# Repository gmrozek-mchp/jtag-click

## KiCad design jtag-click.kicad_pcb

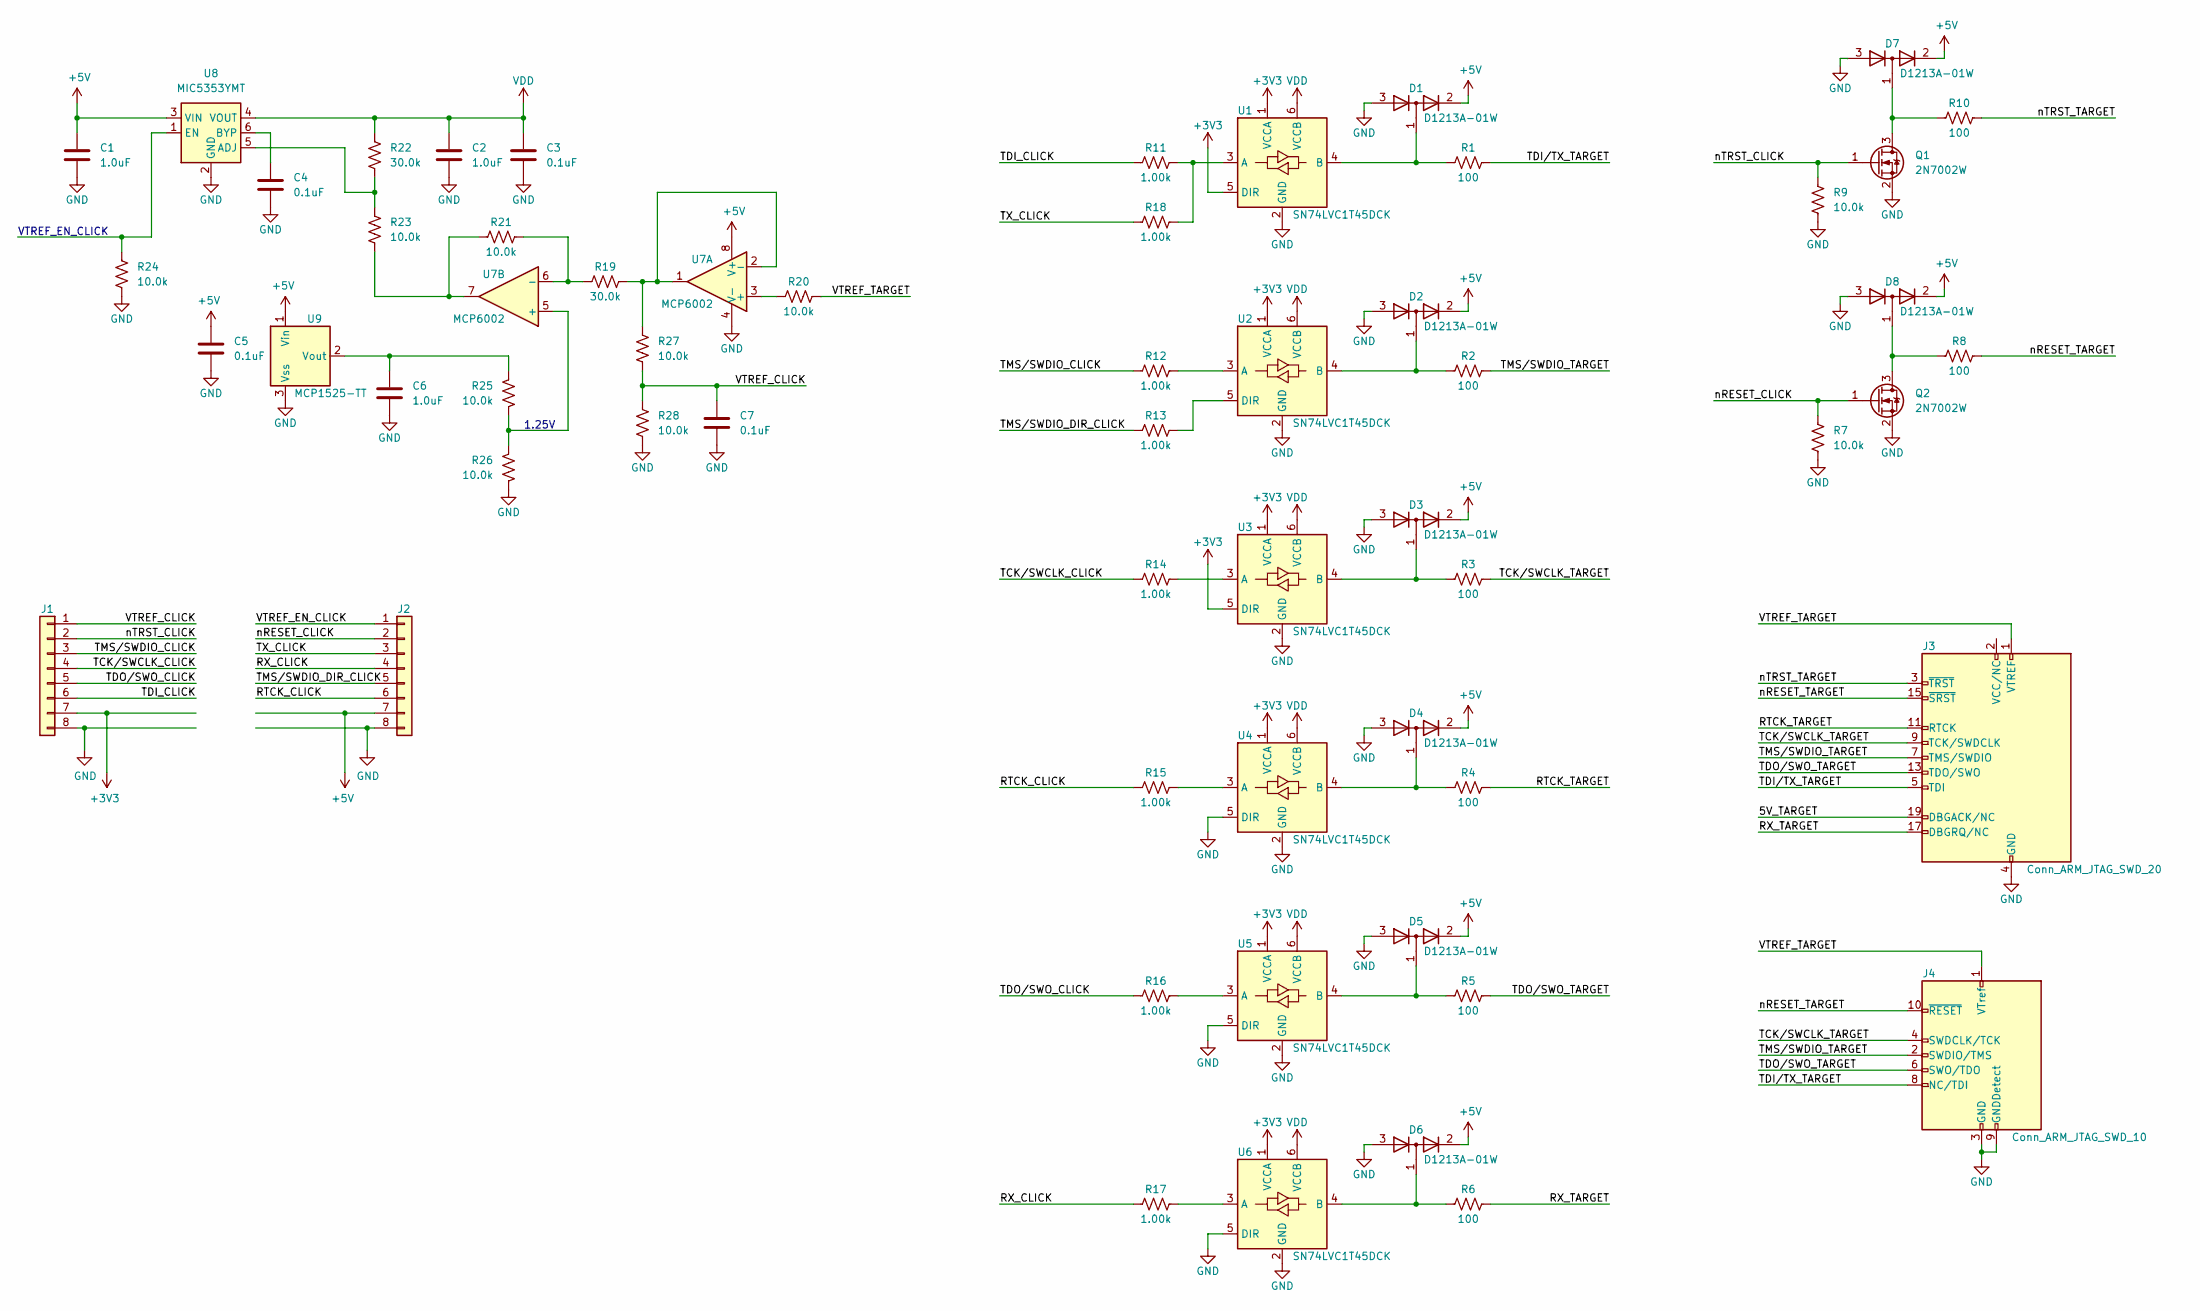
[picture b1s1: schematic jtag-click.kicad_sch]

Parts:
C1, C2, C6: 1.0uF; C_0603_1608Metric
C3, C4, C5, C7: 0.1uF; C_0402_1005Metric
D1, D2, D3, D4, D5, D6, D7, D8: D1213A-01W; SOT-323_SC-70
J1, J2: Conn_01x08; PinHeader_1x08_P2.54mm_Vertical
J3: Conn_ARM_JTAG_SWD_20; IDC-Header_2x10_P2.54mm_Horizontal
J4: Conn_ARM_JTAG_SWD_10; PinHeader_2x05_P1.27mm_Vertical
Q1, Q2: 2N7002W; SOT-323_SC-70
R1, R2, R3, R4, R5, R6, R8, R10: 100; R_0402_1005Metric
R7, R9, R20, R21, R23, R24, R25, R26, R27, R28: 10.0k; R_0402_1005Metric
R11, R12, R13, R14, R15, R16, R17, R18: 1.00k; R_0402_1005Metric
R19, R22: 30.0k; R_0402_1005Metric
U1, U2, U3, U4, U5, U6: SN74LVC1T45DCK; SOT-363_SC-70-6
U7: MCP6002; DFN-8-1EP_3x2mm_P0.5mm_EP1.75x1.45mm
U8: MIC5353YMT; MLF-6-1EP_1.6x1.6mm_P0.5mm_EP0.5x1.26mm
U9: MCP1525-TT; SOT-23

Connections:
+3V3: J1.7, U1.1 (VCCA), U1.5 (DIR), U2.1 (VCCA), U3.1 (VCCA), U3.5 (DIR), U4.1 (VCCA), U5.1 (VCCA), U6.1 (VCCA)
+5V: C1.1, C5.1, D1.2 (K), D2.2 (K), D3.2 (K), D4.2 (K), D5.2 (K), D6.2 (K), D7.2 (K), D8.2 (K), J2.7, U7.8 (V+), U8.3 (VIN), U9.1 (Vin)
/5V_TARGET: J3.19 (DBGACK/NC)
/RTCK_CLICK: J2.6, R15.1
/RTCK_TARGET: J3.11 (RTCK), R4.2
/RX_CLICK: J2.4, R17.1
/RX_TARGET: J3.17 (DBGRQ/NC), R6.2
/TCK/SWCLK_CLICK: J1.4, R14.1
/TCK/SWCLK_TARGET: J3.9 (TCK/SWDCLK), J4.4 (SWDCLK/TCK), R3.2
/TDI_CLICK: J1.6, R11.1
/TDI/TX_TARGET: J3.5 (TDI), J4.8 (NC/TDI), R1.2
/TDO/SWO_CLICK: J1.5, R16.1
/TDO/SWO_TARGET: J3.13 (TDO/SWO), J4.6 (SWO/TDO), R5.2
/TMS/SWDIO_CLICK: J1.3, R12.1
/TMS/SWDIO_DIR_CLICK: J2.5, R13.1
/TMS/SWDIO_TARGET: J3.7 (TMS/SWDIO), J4.2 (SWDIO/TMS), R2.2
/TX_CLICK: J2.3, R18.1
/VTREF_CLICK: C7.1, J1.1, R27.2, R28.1
/VTREF_EN_CLICK: J2.1
/VTREF_TARGET: J3.1 (VTREF), J4.1 (VTref), R20.2
/nRESET_CLICK: J2.2, Q2.1 (G), R7.1
/nRESET_TARGET: J3.15 (~SRST), J4.10 (~RESET), R8.2
/nTRST_CLICK: J1.2, Q1.1 (G), R9.1
/nTRST_TARGET: J3.3 (~TRST), R10.2
GND: C1.2, C2.2, C3.2, C4.2, C5.2, C6.2, C7.2, D1.3 (A), D2.3 (A), D3.3 (A), D4.3 (A), D5.3 (A), D6.3 (A), D7.3 (A), D8.3 (A), J1.8, J2.8, J3.4 (GND), J3.6 (GND), J3.8 (GND), J3.10 (GND), J3.12 (GND), J3.14 (GND), J3.16 (GND), J3.18 (GND), J3.20 (GND), J4.3 (GND), J4.5 (GND), J4.9 (GNDDetect), Q1.2 (S), Q2.2 (S), R7.2, R9.2, R24.2, R26.2, R28.2, U1.2 (GND), U2.2 (GND), U3.2 (GND), U4.2 (GND), U4.5 (DIR), U5.2 (GND), U5.5 (DIR), U6.2 (GND), U6.5 (DIR), U7.4 (V-), U7.9 (V-), U8.2 (GND), U8.7 (GND), U9.3 (Vss)
unnamed: D1.1 (common), R1.1, U1.4 (B)
unnamed: D2.1 (common), R2.1, U2.4 (B)
unnamed: D3.1 (common), R3.1, U3.4 (B)
unnamed: D4.1 (common), R4.1, U4.4 (B)
unnamed: D5.1 (common), R5.1, U5.4 (B)
unnamed: D6.1 (common), R6.1, U6.4 (B)
unnamed: D7.1 (common), Q1.3 (D), R10.1
unnamed: D8.1 (common), Q2.3 (D), R8.1
unnamed: R21.1, R23.2, U7.7
unnamed: R11.2, R18.2, U1.3 (A)
unnamed: R12.2, U2.3 (A)
unnamed: R13.2, U2.5 (DIR)
unnamed: R14.2, U3.3 (A)
unnamed: R15.2, U4.3 (A)
unnamed: R16.2, U5.3 (A)
unnamed: R17.2, U6.3 (A)
unnamed: R20.1, U7.3 (+)
unnamed: R19.2, R27.1, U7.1, U7.2 (-)
unnamed: R25.2, R26.1, U7.5 (+)
unnamed: R19.1, R21.2, U7.6 (-)
unnamed: R22.2, R23.1, U8.5 (ADJ)
unnamed: C4.1, U8.6 (BYP)
unnamed: R24.1, U8.1 (EN)
unnamed: C6.1, R25.1, U9.2 (Vout)
VDD: C2.1, C3.1, R22.1, U1.6 (VCCB), U2.6 (VCCB), U3.6 (VCCB), U4.6 (VCCB), U5.6 (VCCB), U6.6 (VCCB), U8.4 (VOUT)

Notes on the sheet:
VTREF_EN_CLICK
1.25V

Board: 2 copper layers, 58 parts (2 on the bottom side), 48 nets, no tracks yet.

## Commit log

2023-09-16 Initial commit of blank kicad project
2023-09-18 Work in progress
2023-09-18 Plot schematic
2023-09-18 Add VTREF_CLICK voltage divider for sensing VTREF
2023-09-18 Change Vp of clamp diodes to 5V to prevent current flow if VDD is disabled.
